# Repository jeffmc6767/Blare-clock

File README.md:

Blare clock
-

This is my alarm clock with a display, buzzer and 4 buttons to customize it.         

Features:
-

- It shows current time
- Custom alarms
- adjustable with switches.

Quick start:
-

1. Get all the needed parts
2. Solder the pcb - exclude the switches right now.
3. Place the heatset inserts into the case, and install the PCB
4. Next, solder the switches, and place the top layer under the switches.
5. DONE! 

Image gallery:
-

My case: 

My PCB: 

BOM: 

1x PCB: 5$
1x Seeed XIAO ESP32C3
4x MX-Style Keyboard Switches
4x White Blank DSA Keycaps
0x Through-Hole 1N4148 Diodes
1x 2.25in TFT Screen
1x 3.3V Piezo Buzzer
1x 2.54mm 8 Pin Male Header (For connecting your screen)
8x 20cm Female-Female Jumper Wires (For connecting your screen off of the pcb)
4x M3x5x4 Heatset Inserts
4x M3x8mm Screws
4x M3x16mm Screws

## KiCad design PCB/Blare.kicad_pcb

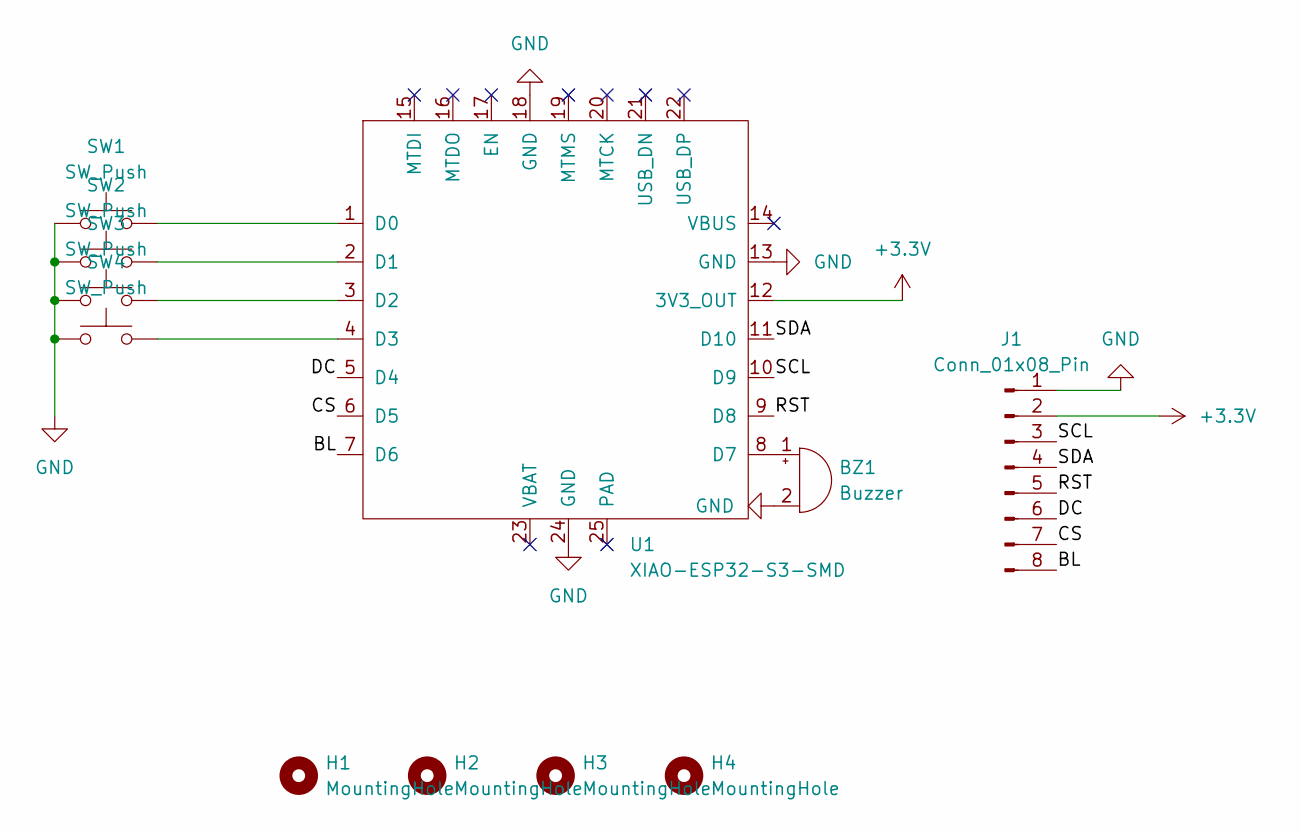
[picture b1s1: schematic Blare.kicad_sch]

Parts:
BZ1: Buzzer; Buzzer_12x9.5RM7.6
H1, H2, H3, H4: MountingHole; MountingHole_3.2mm_M3
J1: Conn_01x08_Pin; PinSocket_1x08_P2.54mm_Vertical
SW1, SW2, SW3, SW4: SW_Push; SW_Cherry_MX_1.00u_PCB-Gateron-KS-3x switch
U1: XIAO-ESP32-S3-SMD

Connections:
+3.3V: J1.2, U1.12 (3V3_OUT)
/BL: J1.8, U1.7 (D6)
/CS: J1.7, U1.6 (D5)
/DC: J1.6, U1.5 (D4)
/RST: J1.5, U1.9 (D8)
/SCL: J1.3, U1.10 (D9)
/SDA: J1.4, U1.11 (D10)
GND: BZ1.2 (-), J1.1, SW1.1, SW2.1, SW3.1, SW4.1, U1.13 (GND), U1.18 (GND), U1.24 (GND)
unnamed: BZ1.1 (+), U1.8 (D7)
unnamed: SW1.2, U1.1 (D0)
unnamed: SW2.2, U1.2 (D1)
unnamed: SW3.2, U1.3 (D2)
unnamed: SW4.2, U1.4 (D3)

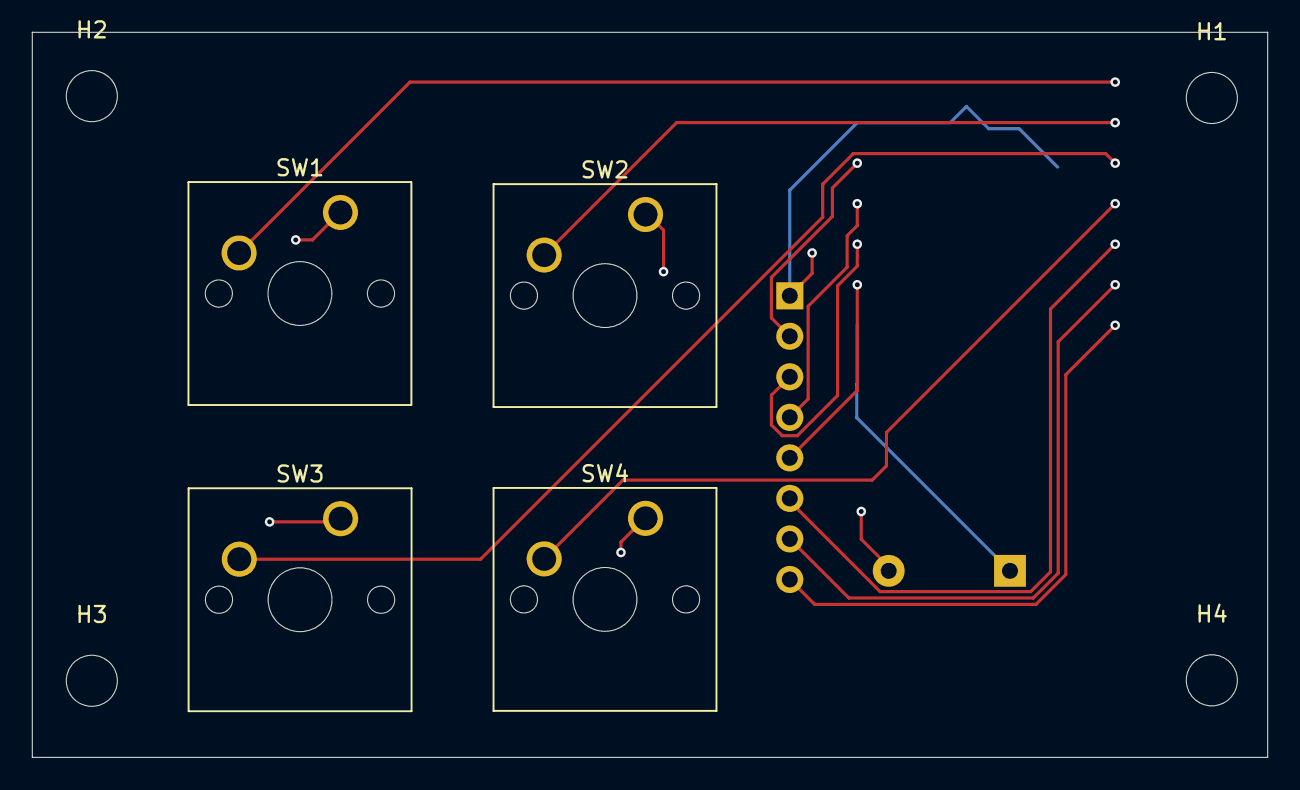
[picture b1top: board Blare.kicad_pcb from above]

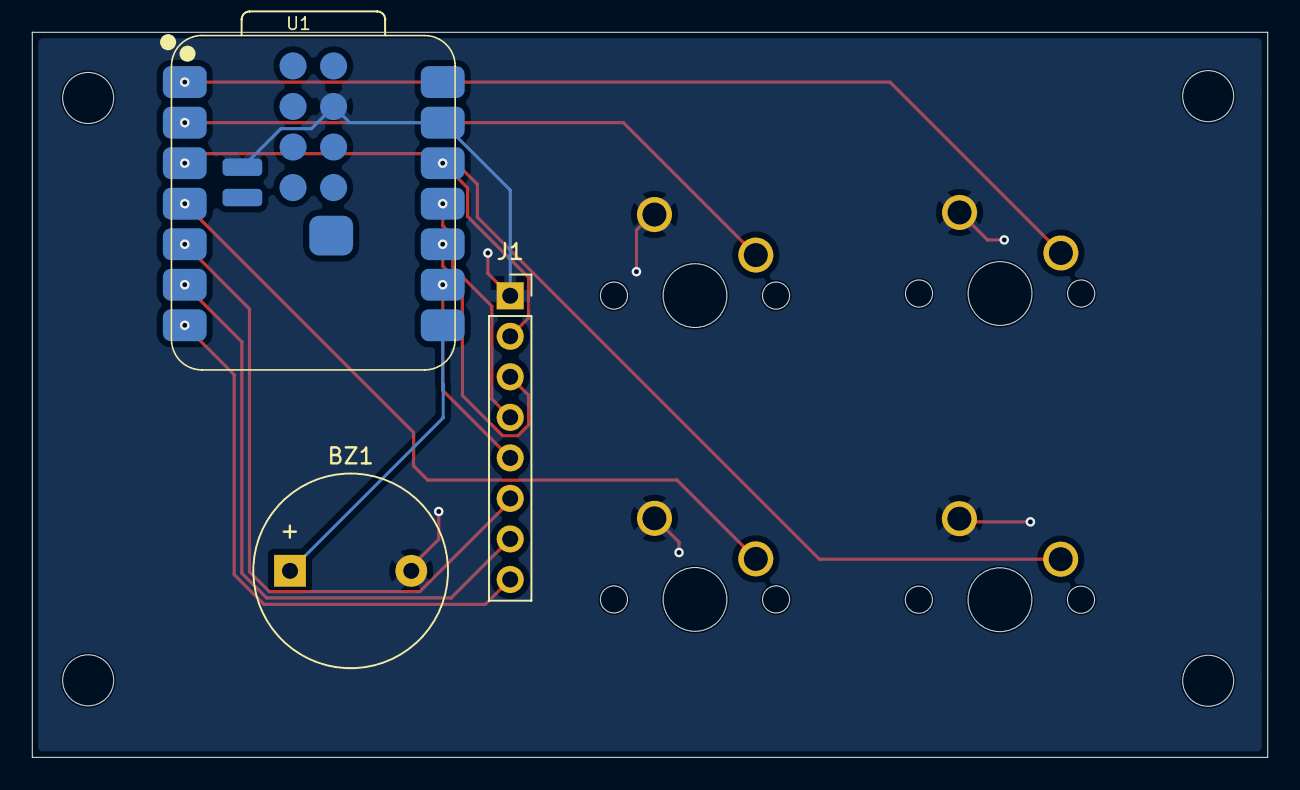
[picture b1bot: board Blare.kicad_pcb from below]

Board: 2 copper layers, 77.4 x 45.4 mm, 11 parts (3 on the bottom side), 13 nets.
